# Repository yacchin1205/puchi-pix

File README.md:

# Puchi-Pix (ぷちぴく)

A tiny pixel art display kit powered by STM32G030F6P, with a 96x64 OLED (SSD1331) or TFT display.

## Concept

Puchi-Pix was born from a simple desire: to carry pixel art animations in your pocket.

It pairs an STM32G030F6P with a small OLED, targeting a keychain-sized form factor. Rather than a coin cell with its tedious battery swaps, the board integrates a LiPo charger on-board — unusual for something this small, but essential for a device meant to live in your pocket. Exposed GPIO and an onboard accelerometer also make it a capable dev board.

The STM32G030F6P has just 32KB of flash. Fitting animated pixel art into that space demands inter-frame delta compression, 4-bit palettes, and every byte counted. The kind of constraint that once made a project like this feel out of reach for a weekend hack.

Enter the age of coding agents. What used to take careful hand-optimization now becomes a conversation — iterate on compression schemes, generate frame data, and push against hardware limits at the speed of thought. The constraint doesn't go away, but it stops being a barrier and starts being a craft.

Puchi-Pix is a project built for this era — constrained hardware, creative ambition, and an AI coding agent to bridge the gap.

## STM32G030 BOOT0 pin issue

The factory default option bytes have `nBOOT_SEL=1`, which ignores the physical BOOT0 pin. A fresh (empty flash) chip boots into the bootloader automatically, but once firmware is written, the BOOT button has no effect.

Before the first firmware upload, set `nBOOT_SEL=0` via STM32CubeProgrammer CLI:

```bash
STM32_Programmer_CLI -c port=/dev/cu.usbserial-XXXXX br=115200 -ob nBOOT_SEL=0
```

Verify with:

```bash
STM32_Programmer_CLI -c port=/dev/cu.usbserial-XXXXX br=115200 -ob displ
```

`nBOOT_SEL : 0x0 (BOOT0 signal is defined by BOOT0 pin value (legacy mode))` means BOOT+RST will work.

## ESP32 upload fails despite BOOT+RST

On the ESP32 board, entering the bootloader with BOOT+RST sometimes doesn't take — the upload hangs at `Connecting...` for a while and then errors out with:

```
A fatal error occurred: Failed to connect to ESP32-C3: No serial data received.
```

BOOT (GPIO9) is a strapping pin sampled the moment reset is released, so what matters is the button order, not how long anything is held:

1. Press and **hold** BOOT
2. Press and release RST while still holding BOOT
3. Wait a beat, **then** release BOOT — releasing it before (or together with) RST boots the app normally instead
4. Give the USB port a second or two to re-enumerate, then start the upload

If it still fails, power-cycle the board completely and enter the bootloader
before plugging USB back in (on battery power) — this connects reliably:

1. Unplug USB
2. Slide switch OFF, then back ON
3. BOOT+RST (sequence above)
4. Plug USB back in, wait for the port to appear, then start the upload

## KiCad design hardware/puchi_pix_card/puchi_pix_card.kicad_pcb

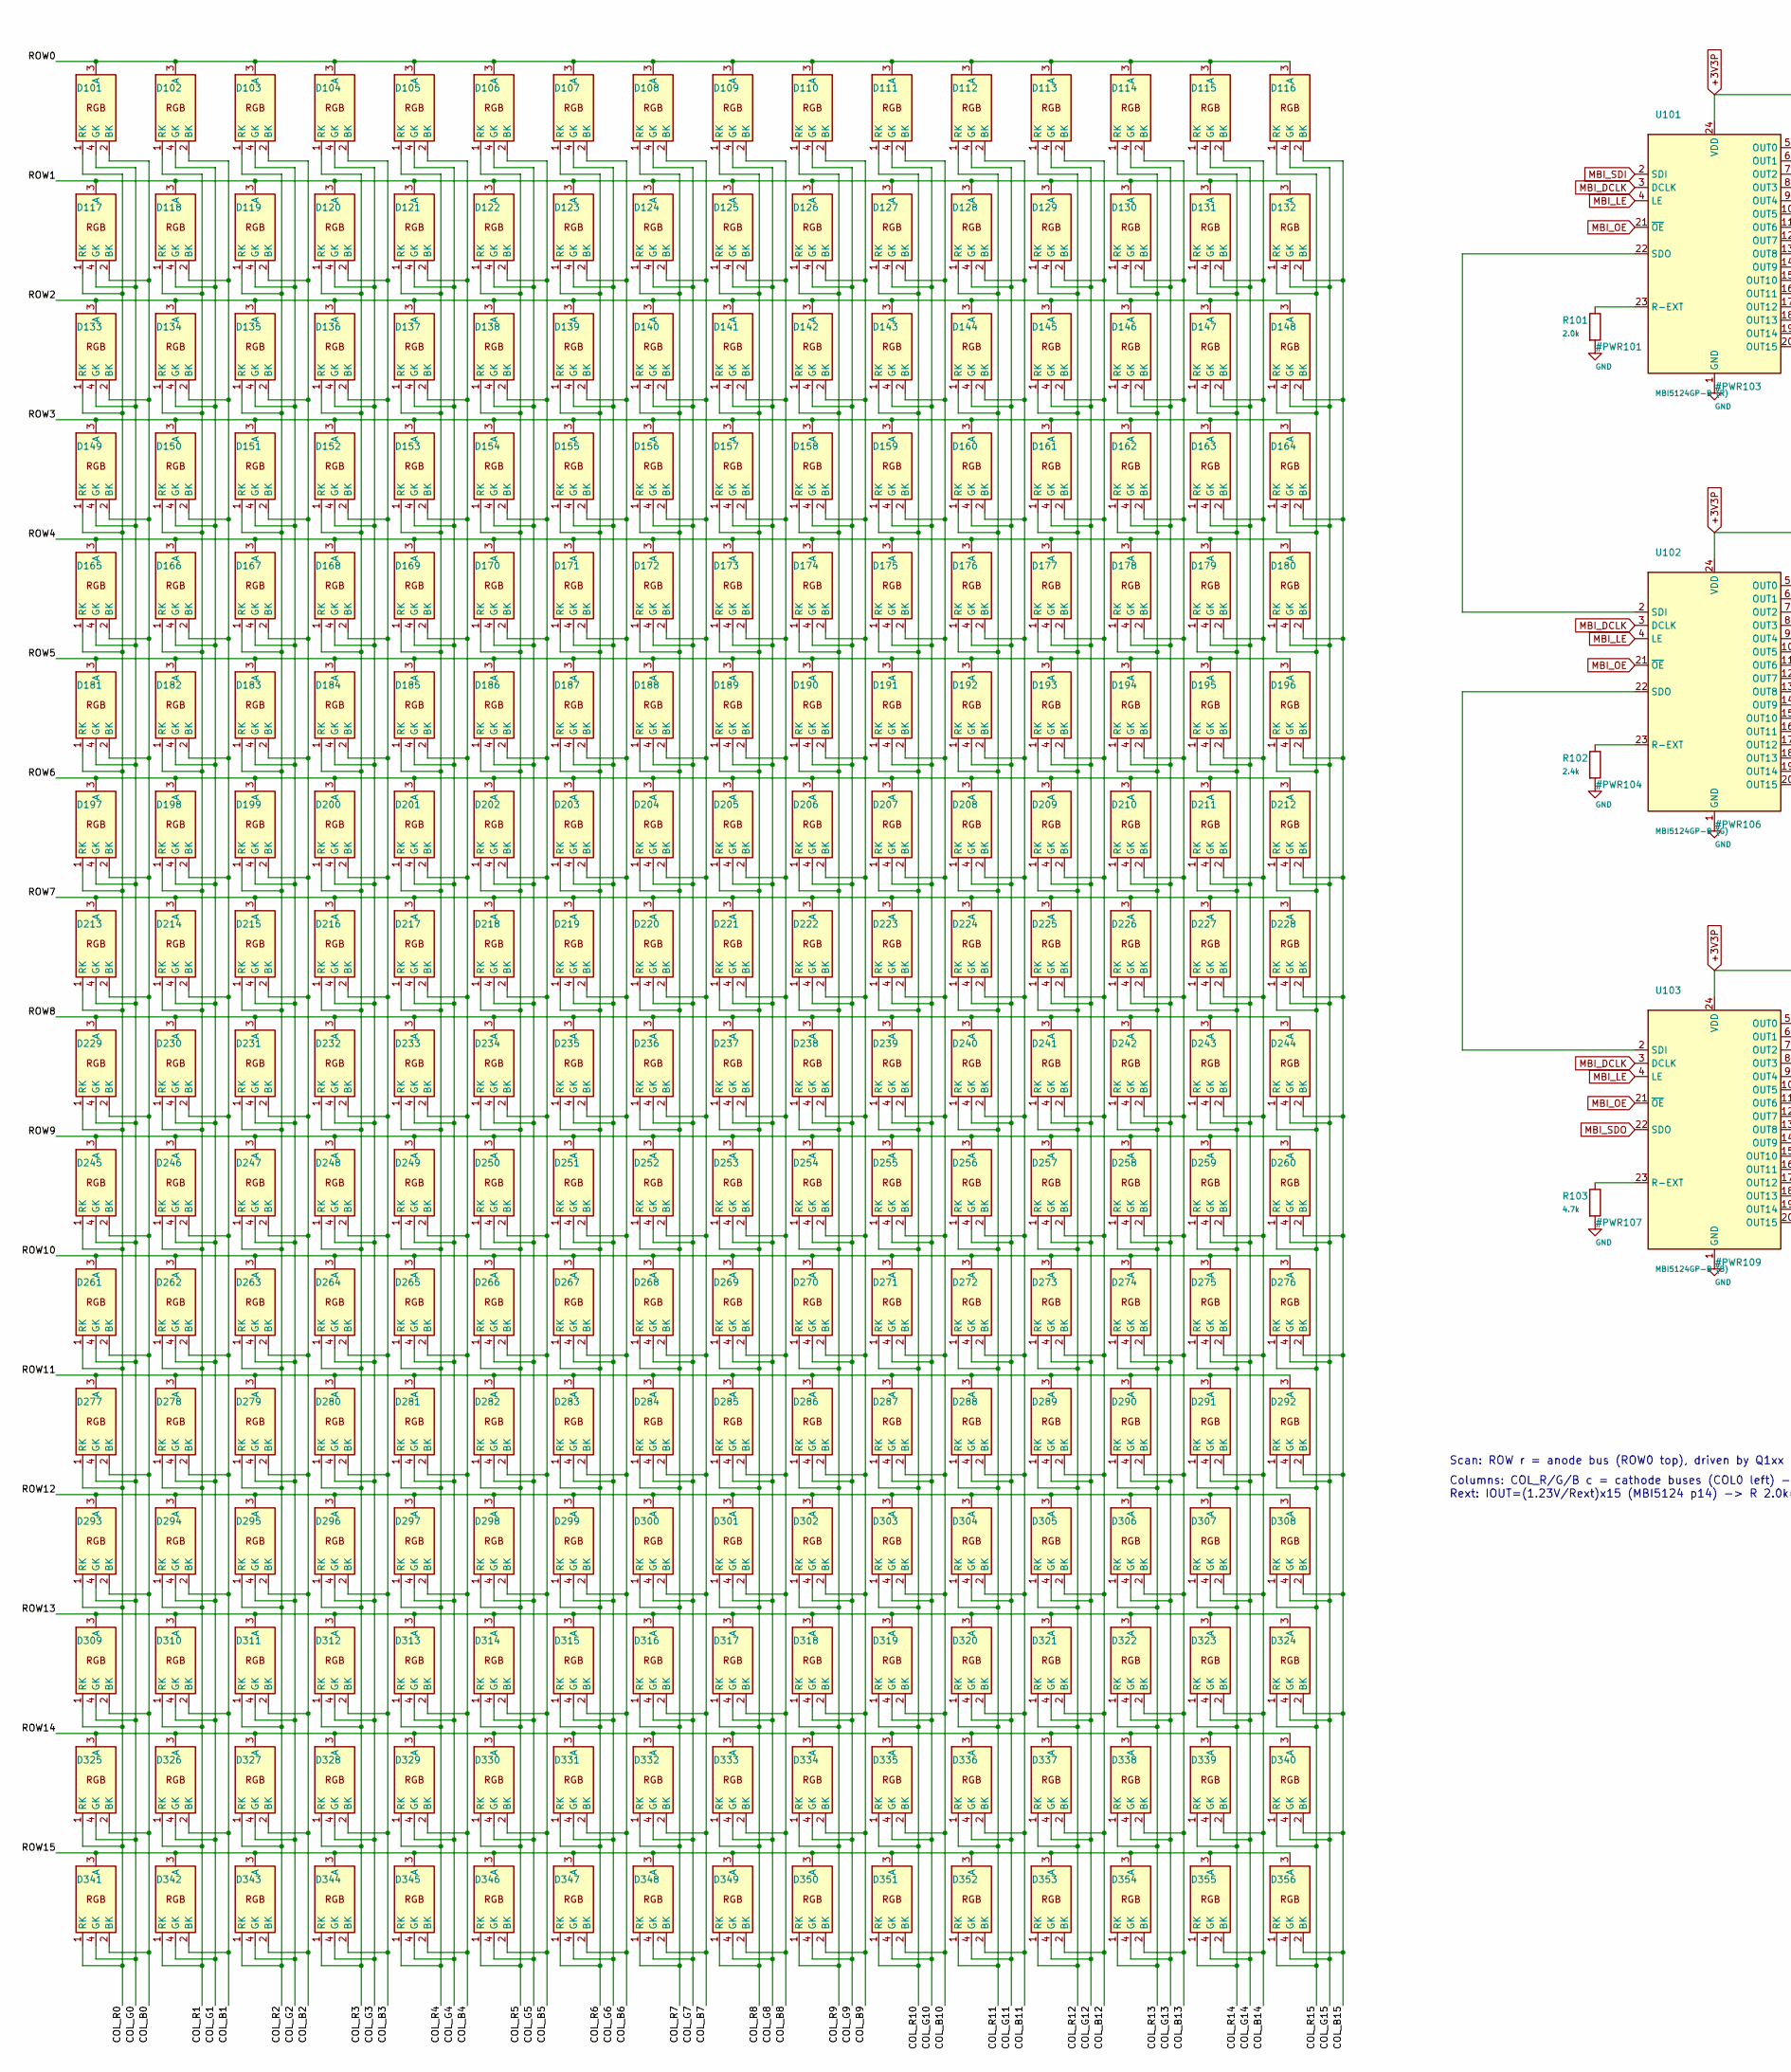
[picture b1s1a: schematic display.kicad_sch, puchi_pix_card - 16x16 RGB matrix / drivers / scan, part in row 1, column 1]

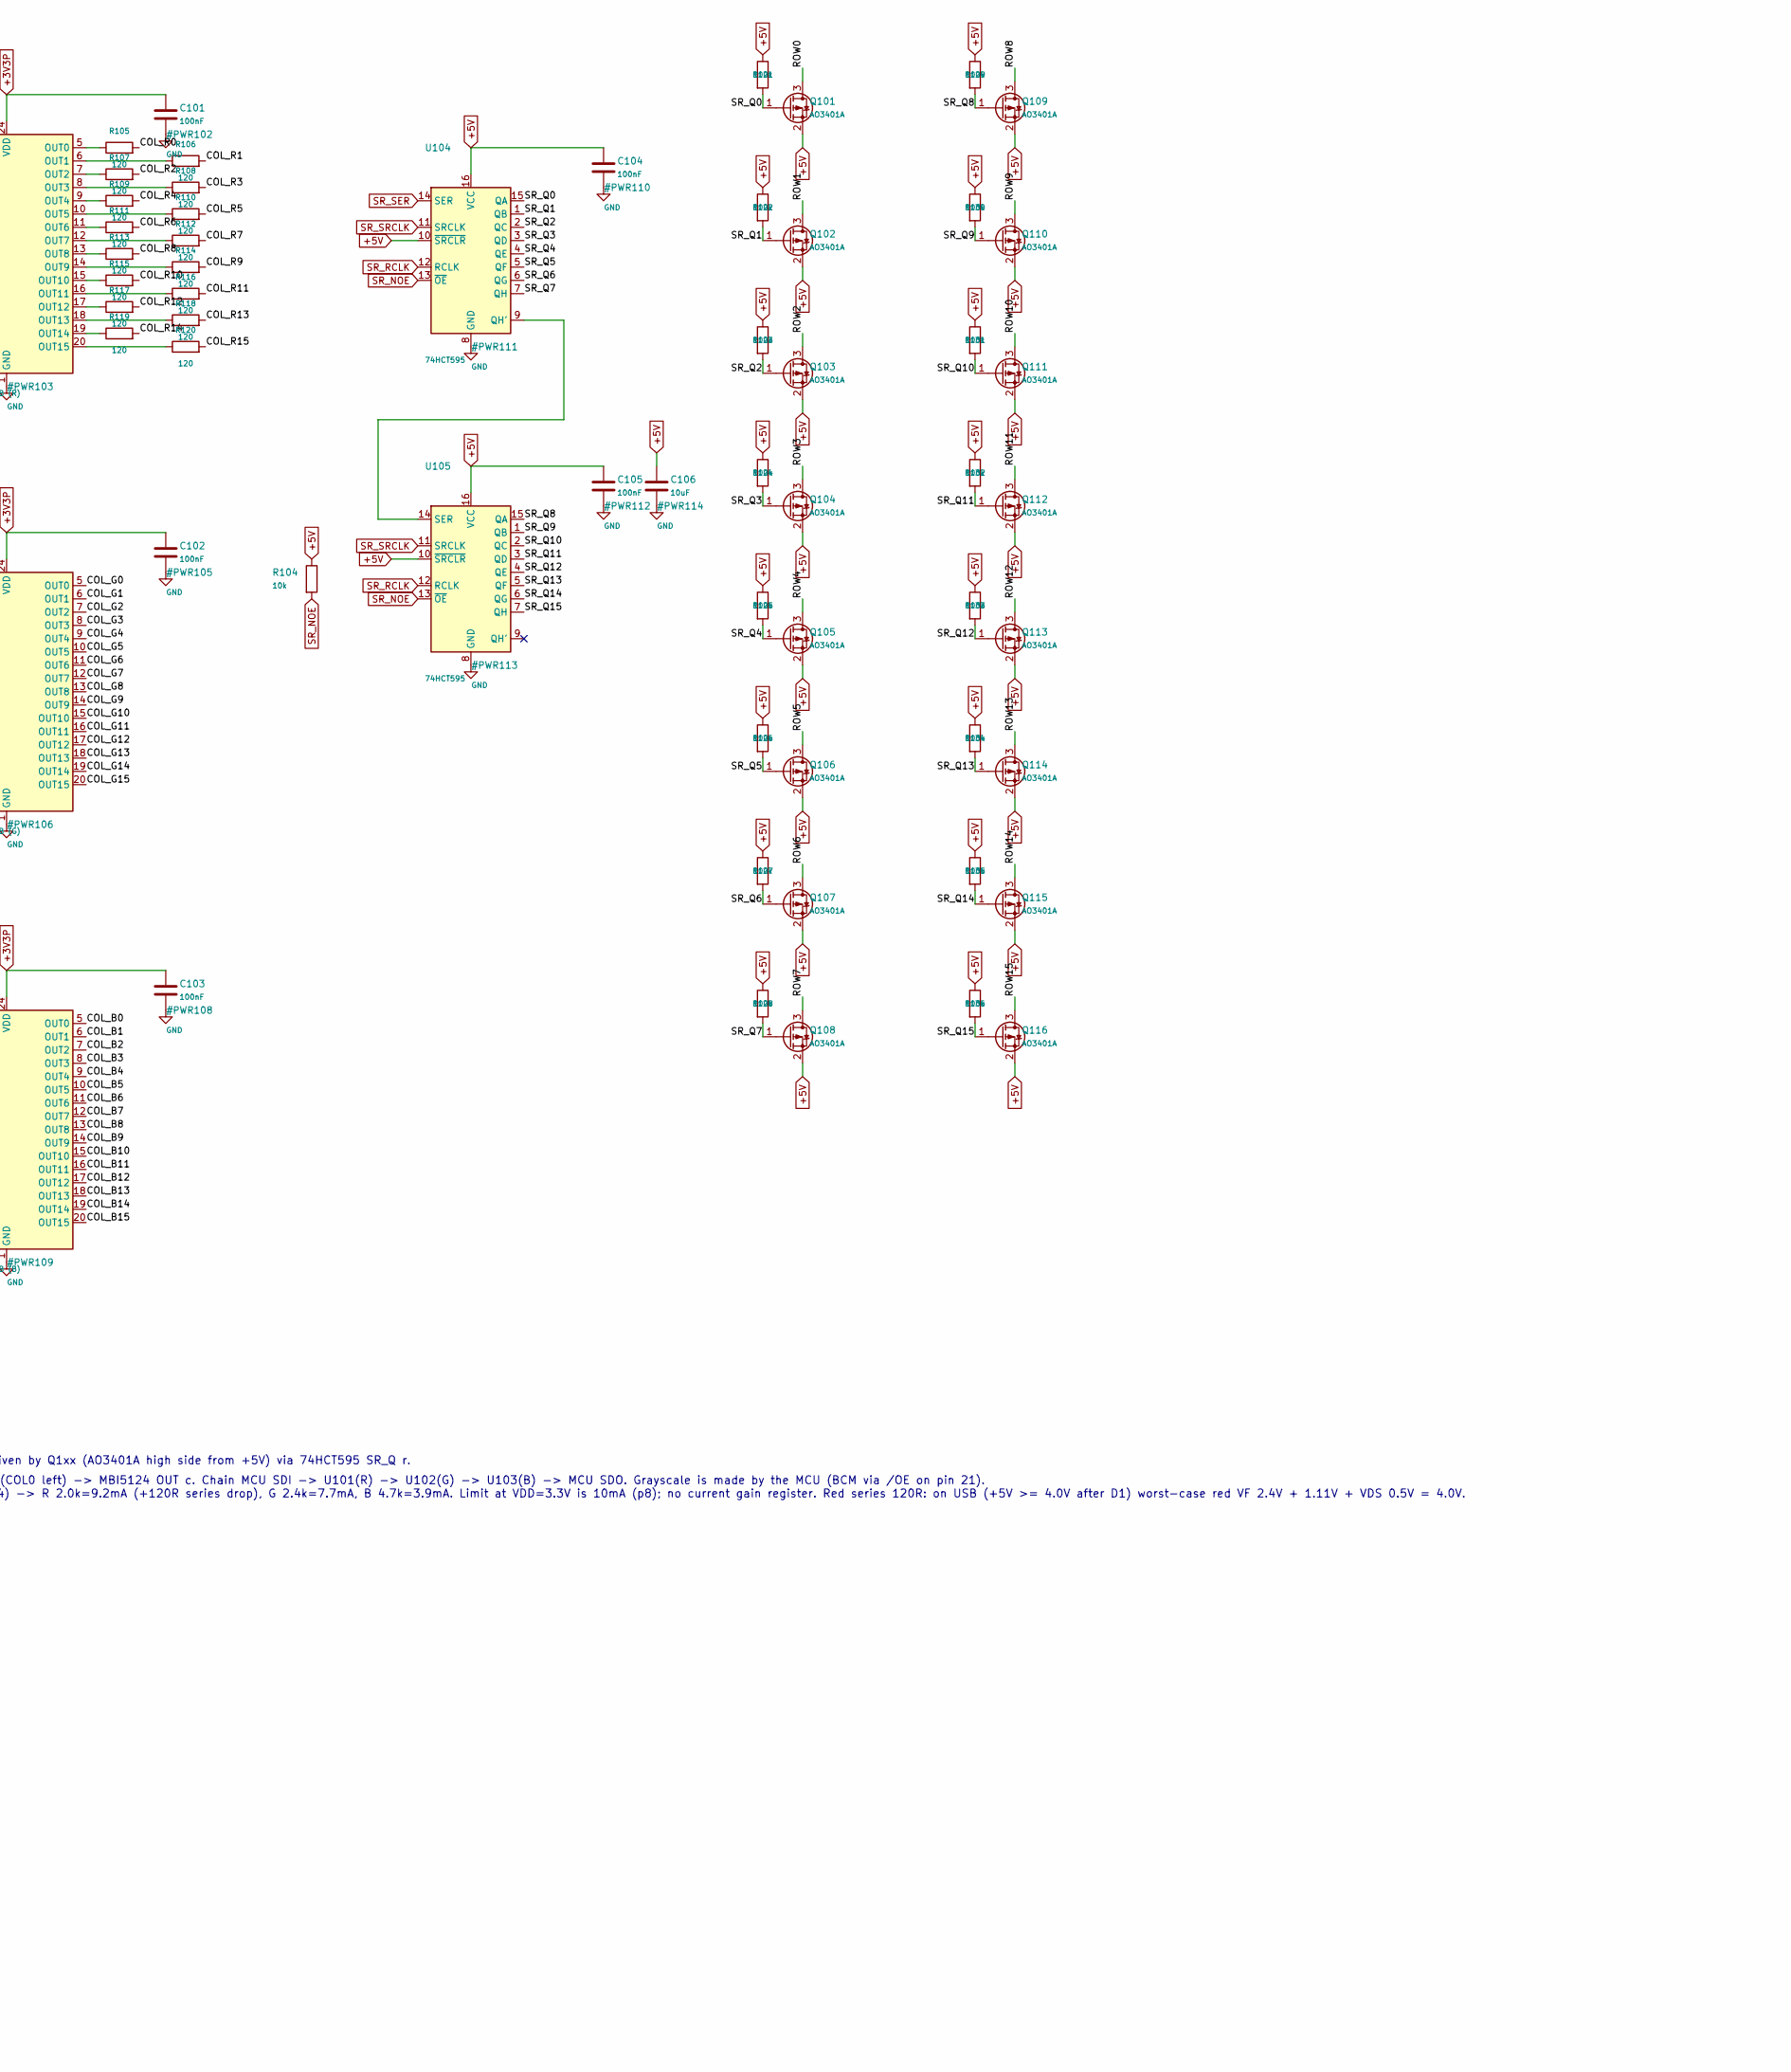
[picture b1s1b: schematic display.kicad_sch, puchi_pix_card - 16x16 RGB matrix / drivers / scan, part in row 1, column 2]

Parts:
C101, C102, C103, C104, C105: 100nF; C_0402_1005Metric; LCSC C309458
C106: 10uF; C_0603_1608Metric; LCSC C96446
D101, D102, D103, D104, D105, D106, D107, D108, D109, D110, D111, D112, D113, D114, D115, D116, D117, D118, D119, D120, D121, D122, D123, D124, D125, D126, D127, D128, D129, D130, D131, D132, D133, D134, D135, D136, D137, D138, D139, D140, D141, D142, D143, D144, D145, D146, D147, D148, D149, D150, D151, D152, D153, D154, D155, D156, D157, D158, D159, D160, D161, D162, D163, D164, D165, D166, D167, D168, D169, D170, D171, D172, D173, D174, D175, D176, D177, D178, D179, D180, D181, D182, D183, D184, D185, D186, D187, D188, D189, D190, D191, D192, D193, D194, D195, D196, D197, D198, D199, D200, D201, D202, D203, D204, D205, D206, D207, D208, D209, D210, D211, D212, D213, D214, D215, D216, D217, D218, D219, D220, D221, D222, D223, D224, D225, D226, D227, D228, D229, D230, D231, D232, D233, D234, D235, D236, D237, D238, D239, D240, D241, D242, D243, D244, D245, D246, D247, D248, D249, D250, D251, D252, D253, D254, D255, D256, D257, D258, D259, D260, D261, D262, D263, D264, D265, D266, D267, D268, D269, D270, D271, D272, D273, D274, D275, D276, D277, D278, D279, D280, D281, D282, D283, D284, D285, D286, D287, D288, D289, D290, D291, D292, D293, D294, D295, D296, D297, D298, D299, D300, D301, D302, D303, D304, D305, D306, D307, D308, D309, D310, D311, D312, D313, D314, D315, D316, D317, D318, D319, D320, D321, D322, D323, D324, D325, D326, D327, D328, D329, D330, D331, D332, D333, D334, D335, D336, D337, D338, D339, D340, D341, D342, D343, D344, D345, D346, D347, D348, D349, D350, D351, D352, D353, D354, D355, D356: FM-B2020RGBA-HG; LED_FM-B2020RGBA; LCSC C42421005
Q101, Q102, Q103, Q104, Q105, Q106, Q107, Q108, Q109, Q110, Q111, Q112, Q113, Q114, Q115, Q116: AO3401A; SOT-23; LCSC C15127
R101: 2.0k; R_0402_1005Metric; LCSC C4109
R102: 2.4k; R_0402_1005Metric; LCSC C25882
R103: 4.7k; R_0402_1005Metric; LCSC C25900
R104: 10k; R_0402_1005Metric; LCSC C25744
R105, R106, R107, R108, R109, R110, R111, R112, R113, R114, R115, R116, R117, R118, R119, R120: 120; R_0402_1005Metric; LCSC C25079
R121, R122, R123, R124, R125, R126, R127, R128, R129, R130, R131, R132, R133, R134, R135, R136: 100k; R_0402_1005Metric; LCSC C25741
U101: MBI5124GP-B (R); SSOP24L-150-0.64; LCSC C256866
U102: MBI5124GP-B (G); SSOP24L-150-0.64; LCSC C256866
U103: MBI5124GP-B (B); SSOP24L-150-0.64; LCSC C256866
U104, U105: 74HCT595; SOIC-16_3.9x9.9mm_P1.27mm; LCSC C282339

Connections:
+3V3P: C101.1, C102.1, C103.1, U101.24 (VDD), U102.24 (VDD), U103.24 (VDD); also elsewhere on the board
+5V: C104.1, C105.1, C106.1, Q101.2 (S), Q102.2 (S), Q103.2 (S), Q104.2 (S), Q105.2 (S), Q106.2 (S), Q107.2 (S), Q108.2 (S), Q109.2 (S), Q110.2 (S), Q111.2 (S), Q112.2 (S), Q113.2 (S), Q114.2 (S), Q115.2 (S), Q116.2 (S), R104.1, R121.1, R122.1, R123.1, R124.1, R125.1, R126.1, R127.1, R128.1, R129.1, R130.1, R131.1, R132.1, R133.1, R134.1, R135.1, R136.1, U104.10 (~SRCLR), U104.16 (VCC), U105.10 (~SRCLR), U105.16 (VCC); also elsewhere on the board
/display/COL_B0: D101.2 (BK), D117.2 (BK), D133.2 (BK), D149.2 (BK), D165.2 (BK), D181.2 (BK), D197.2 (BK), D213.2 (BK), D229.2 (BK), D245.2 (BK), D261.2 (BK), D277.2 (BK), D293.2 (BK), D309.2 (BK), D325.2 (BK), D341.2 (BK), U103.5 (OUT0)
/display/COL_B1: D102.2 (BK), D118.2 (BK), D134.2 (BK), D150.2 (BK), D166.2 (BK), D182.2 (BK), D198.2 (BK), D214.2 (BK), D230.2 (BK), D246.2 (BK), D262.2 (BK), D278.2 (BK), D294.2 (BK), D310.2 (BK), D326.2 (BK), D342.2 (BK), U103.6 (OUT1)
/display/COL_B2: D103.2 (BK), D119.2 (BK), D135.2 (BK), D151.2 (BK), D167.2 (BK), D183.2 (BK), D199.2 (BK), D215.2 (BK), D231.2 (BK), D247.2 (BK), D263.2 (BK), D279.2 (BK), D295.2 (BK), D311.2 (BK), D327.2 (BK), D343.2 (BK), U103.7 (OUT2)
/display/COL_B3: D104.2 (BK), D120.2 (BK), D136.2 (BK), D152.2 (BK), D168.2 (BK), D184.2 (BK), D200.2 (BK), D216.2 (BK), D232.2 (BK), D248.2 (BK), D264.2 (BK), D280.2 (BK), D296.2 (BK), D312.2 (BK), D328.2 (BK), D344.2 (BK), U103.8 (OUT3)
/display/COL_B4: D105.2 (BK), D121.2 (BK), D137.2 (BK), D153.2 (BK), D169.2 (BK), D185.2 (BK), D201.2 (BK), D217.2 (BK), D233.2 (BK), D249.2 (BK), D265.2 (BK), D281.2 (BK), D297.2 (BK), D313.2 (BK), D329.2 (BK), D345.2 (BK), U103.9 (OUT4)
/display/COL_B5: D106.2 (BK), D122.2 (BK), D138.2 (BK), D154.2 (BK), D170.2 (BK), D186.2 (BK), D202.2 (BK), D218.2 (BK), D234.2 (BK), D250.2 (BK), D266.2 (BK), D282.2 (BK), D298.2 (BK), D314.2 (BK), D330.2 (BK), D346.2 (BK), U103.10 (OUT5)
/display/COL_B6: D107.2 (BK), D123.2 (BK), D139.2 (BK), D155.2 (BK), D171.2 (BK), D187.2 (BK), D203.2 (BK), D219.2 (BK), D235.2 (BK), D251.2 (BK), D267.2 (BK), D283.2 (BK), D299.2 (BK), D315.2 (BK), D331.2 (BK), D347.2 (BK), U103.11 (OUT6)
/display/COL_B7: D108.2 (BK), D124.2 (BK), D140.2 (BK), D156.2 (BK), D172.2 (BK), D188.2 (BK), D204.2 (BK), D220.2 (BK), D236.2 (BK), D252.2 (BK), D268.2 (BK), D284.2 (BK), D300.2 (BK), D316.2 (BK), D332.2 (BK), D348.2 (BK), U103.12 (OUT7)
/display/COL_B8: D109.2 (BK), D125.2 (BK), D141.2 (BK), D157.2 (BK), D173.2 (BK), D189.2 (BK), D205.2 (BK), D221.2 (BK), D237.2 (BK), D253.2 (BK), D269.2 (BK), D285.2 (BK), D301.2 (BK), D317.2 (BK), D333.2 (BK), D349.2 (BK), U103.13 (OUT8)
/display/COL_B9: D110.2 (BK), D126.2 (BK), D142.2 (BK), D158.2 (BK), D174.2 (BK), D190.2 (BK), D206.2 (BK), D222.2 (BK), D238.2 (BK), D254.2 (BK), D270.2 (BK), D286.2 (BK), D302.2 (BK), D318.2 (BK), D334.2 (BK), D350.2 (BK), U103.14 (OUT9)
/display/COL_B10: D111.2 (BK), D127.2 (BK), D143.2 (BK), D159.2 (BK), D175.2 (BK), D191.2 (BK), D207.2 (BK), D223.2 (BK), D239.2 (BK), D255.2 (BK), D271.2 (BK), D287.2 (BK), D303.2 (BK), D319.2 (BK), D335.2 (BK), D351.2 (BK), U103.15 (OUT10)
/display/COL_B11: D112.2 (BK), D128.2 (BK), D144.2 (BK), D160.2 (BK), D176.2 (BK), D192.2 (BK), D208.2 (BK), D224.2 (BK), D240.2 (BK), D256.2 (BK), D272.2 (BK), D288.2 (BK), D304.2 (BK), D320.2 (BK), D336.2 (BK), D352.2 (BK), U103.16 (OUT11)
/display/COL_B12: D113.2 (BK), D129.2 (BK), D145.2 (BK), D161.2 (BK), D177.2 (BK), D193.2 (BK), D209.2 (BK), D225.2 (BK), D241.2 (BK), D257.2 (BK), D273.2 (BK), D289.2 (BK), D305.2 (BK), D321.2 (BK), D337.2 (BK), D353.2 (BK), U103.17 (OUT12)
/display/COL_B13: D114.2 (BK), D130.2 (BK), D146.2 (BK), D162.2 (BK), D178.2 (BK), D194.2 (BK), D210.2 (BK), D226.2 (BK), D242.2 (BK), D258.2 (BK), D274.2 (BK), D290.2 (BK), D306.2 (BK), D322.2 (BK), D338.2 (BK), D354.2 (BK), U103.18 (OUT13)
/display/COL_B14: D115.2 (BK), D131.2 (BK), D147.2 (BK), D163.2 (BK), D179.2 (BK), D195.2 (BK), D211.2 (BK), D227.2 (BK), D243.2 (BK), D259.2 (BK), D275.2 (BK), D291.2 (BK), D307.2 (BK), D323.2 (BK), D339.2 (BK), D355.2 (BK), U103.19 (OUT14)
/display/COL_B15: D116.2 (BK), D132.2 (BK), D148.2 (BK), D164.2 (BK), D180.2 (BK), D196.2 (BK), D212.2 (BK), D228.2 (BK), D244.2 (BK), D260.2 (BK), D276.2 (BK), D292.2 (BK), D308.2 (BK), D324.2 (BK), D340.2 (BK), D356.2 (BK), U103.20 (OUT15)
/display/COL_G0: D101.4 (GK), D117.4 (GK), D133.4 (GK), D149.4 (GK), D165.4 (GK), D181.4 (GK), D197.4 (GK), D213.4 (GK), D229.4 (GK), D245.4 (GK), D261.4 (GK), D277.4 (GK), D293.4 (GK), D309.4 (GK), D325.4 (GK), D341.4 (GK), U102.5 (OUT0)
/display/COL_G1: D102.4 (GK), D118.4 (GK), D134.4 (GK), D150.4 (GK), D166.4 (GK), D182.4 (GK), D198.4 (GK), D214.4 (GK), D230.4 (GK), D246.4 (GK), D262.4 (GK), D278.4 (GK), D294.4 (GK), D310.4 (GK), D326.4 (GK), D342.4 (GK), U102.6 (OUT1)
/display/COL_G2: D103.4 (GK), D119.4 (GK), D135.4 (GK), D151.4 (GK), D167.4 (GK), D183.4 (GK), D199.4 (GK), D215.4 (GK), D231.4 (GK), D247.4 (GK), D263.4 (GK), D279.4 (GK), D295.4 (GK), D311.4 (GK), D327.4 (GK), D343.4 (GK), U102.7 (OUT2)
/display/COL_G3: D104.4 (GK), D120.4 (GK), D136.4 (GK), D152.4 (GK), D168.4 (GK), D184.4 (GK), D200.4 (GK), D216.4 (GK), D232.4 (GK), D248.4 (GK), D264.4 (GK), D280.4 (GK), D296.4 (GK), D312.4 (GK), D328.4 (GK), D344.4 (GK), U102.8 (OUT3)
/display/COL_G4: D105.4 (GK), D121.4 (GK), D137.4 (GK), D153.4 (GK), D169.4 (GK), D185.4 (GK), D201.4 (GK), D217.4 (GK), D233.4 (GK), D249.4 (GK), D265.4 (GK), D281.4 (GK), D297.4 (GK), D313.4 (GK), D329.4 (GK), D345.4 (GK), U102.9 (OUT4)
/display/COL_G5: D106.4 (GK), D122.4 (GK), D138.4 (GK), D154.4 (GK), D170.4 (GK), D186.4 (GK), D202.4 (GK), D218.4 (GK), D234.4 (GK), D250.4 (GK), D266.4 (GK), D282.4 (GK), D298.4 (GK), D314.4 (GK), D330.4 (GK), D346.4 (GK), U102.10 (OUT5)
/display/COL_G6: D107.4 (GK), D123.4 (GK), D139.4 (GK), D155.4 (GK), D171.4 (GK), D187.4 (GK), D203.4 (GK), D219.4 (GK), D235.4 (GK), D251.4 (GK), D267.4 (GK), D283.4 (GK), D299.4 (GK), D315.4 (GK), D331.4 (GK), D347.4 (GK), U102.11 (OUT6)
/display/COL_G7: D108.4 (GK), D124.4 (GK), D140.4 (GK), D156.4 (GK), D172.4 (GK), D188.4 (GK), D204.4 (GK), D220.4 (GK), D236.4 (GK), D252.4 (GK), D268.4 (GK), D284.4 (GK), D300.4 (GK), D316.4 (GK), D332.4 (GK), D348.4 (GK), U102.12 (OUT7)
/display/COL_G8: D109.4 (GK), D125.4 (GK), D141.4 (GK), D157.4 (GK), D173.4 (GK), D189.4 (GK), D205.4 (GK), D221.4 (GK), D237.4 (GK), D253.4 (GK), D269.4 (GK), D285.4 (GK), D301.4 (GK), D317.4 (GK), D333.4 (GK), D349.4 (GK), U102.13 (OUT8)
/display/COL_G9: D110.4 (GK), D126.4 (GK), D142.4 (GK), D158.4 (GK), D174.4 (GK), D190.4 (GK), D206.4 (GK), D222.4 (GK), D238.4 (GK), D254.4 (GK), D270.4 (GK), D286.4 (GK), D302.4 (GK), D318.4 (GK), D334.4 (GK), D350.4 (GK), U102.14 (OUT9)
/display/COL_G10: D111.4 (GK), D127.4 (GK), D143.4 (GK), D159.4 (GK), D175.4 (GK), D191.4 (GK), D207.4 (GK), D223.4 (GK), D239.4 (GK), D255.4 (GK), D271.4 (GK), D287.4 (GK), D303.4 (GK), D319.4 (GK), D335.4 (GK), D351.4 (GK), U102.15 (OUT10)
/display/COL_G11: D112.4 (GK), D128.4 (GK), D144.4 (GK), D160.4 (GK), D176.4 (GK), D192.4 (GK), D208.4 (GK), D224.4 (GK), D240.4 (GK), D256.4 (GK), D272.4 (GK), D288.4 (GK), D304.4 (GK), D320.4 (GK), D336.4 (GK), D352.4 (GK), U102.16 (OUT11)
/display/COL_G12: D113.4 (GK), D129.4 (GK), D145.4 (GK), D161.4 (GK), D177.4 (GK), D193.4 (GK), D209.4 (GK), D225.4 (GK), D241.4 (GK), D257.4 (GK), D273.4 (GK), D289.4 (GK), D305.4 (GK), D321.4 (GK), D337.4 (GK), D353.4 (GK), U102.17 (OUT12)
/display/COL_G13: D114.4 (GK), D130.4 (GK), D146.4 (GK), D162.4 (GK), D178.4 (GK), D194.4 (GK), D210.4 (GK), D226.4 (GK), D242.4 (GK), D258.4 (GK), D274.4 (GK), D290.4 (GK), D306.4 (GK), D322.4 (GK), D338.4 (GK), D354.4 (GK), U102.18 (OUT13)
/display/COL_G14: D115.4 (GK), D131.4 (GK), D147.4 (GK), D163.4 (GK), D179.4 (GK), D195.4 (GK), D211.4 (GK), D227.4 (GK), D243.4 (GK), D259.4 (GK), D275.4 (GK), D291.4 (GK), D307.4 (GK), D323.4 (GK), D339.4 (GK), D355.4 (GK), U102.19 (OUT14)
/display/COL_G15: D116.4 (GK), D132.4 (GK), D148.4 (GK), D164.4 (GK), D180.4 (GK), D196.4 (GK), D212.4 (GK), D228.4 (GK), D244.4 (GK), D260.4 (GK), D276.4 (GK), D292.4 (GK), D308.4 (GK), D324.4 (GK), D340.4 (GK), D356.4 (GK), U102.20 (OUT15)
/display/COL_R0: D101.1 (RK), D117.1 (RK), D133.1 (RK), D149.1 (RK), D165.1 (RK), D181.1 (RK), D197.1 (RK), D213.1 (RK), D229.1 (RK), D245.1 (RK), D261.1 (RK), D277.1 (RK), D293.1 (RK), D309.1 (RK), D325.1 (RK), D341.1 (RK), R105.2
/display/COL_R1: D102.1 (RK), D118.1 (RK), D134.1 (RK), D150.1 (RK), D166.1 (RK), D182.1 (RK), D198.1 (RK), D214.1 (RK), D230.1 (RK), D246.1 (RK), D262.1 (RK), D278.1 (RK), D294.1 (RK), D310.1 (RK), D326.1 (RK), D342.1 (RK), R106.2
/display/COL_R2: D103.1 (RK), D119.1 (RK), D135.1 (RK), D151.1 (RK), D167.1 (RK), D183.1 (RK), D199.1 (RK), D215.1 (RK), D231.1 (RK), D247.1 (RK), D263.1 (RK), D279.1 (RK), D295.1 (RK), D311.1 (RK), D327.1 (RK), D343.1 (RK), R107.2
/display/COL_R3: D104.1 (RK), D120.1 (RK), D136.1 (RK), D152.1 (RK), D168.1 (RK), D184.1 (RK), D200.1 (RK), D216.1 (RK), D232.1 (RK), D248.1 (RK), D264.1 (RK), D280.1 (RK), D296.1 (RK), D312.1 (RK), D328.1 (RK), D344.1 (RK), R108.2
/display/COL_R4: D105.1 (RK), D121.1 (RK), D137.1 (RK), D153.1 (RK), D169.1 (RK), D185.1 (RK), D201.1 (RK), D217.1 (RK), D233.1 (RK), D249.1 (RK), D265.1 (RK), D281.1 (RK), D297.1 (RK), D313.1 (RK), D329.1 (RK), D345.1 (RK), R109.2
/display/COL_R5: D106.1 (RK), D122.1 (RK), D138.1 (RK), D154.1 (RK), D170.1 (RK), D186.1 (RK), D202.1 (RK), D218.1 (RK), D234.1 (RK), D250.1 (RK), D266.1 (RK), D282.1 (RK), D298.1 (RK), D314.1 (RK), D330.1 (RK), D346.1 (RK), R110.2
/display/COL_R6: D107.1 (RK), D123.1 (RK), D139.1 (RK), D155.1 (RK), D171.1 (RK), D187.1 (RK), D203.1 (RK), D219.1 (RK), D235.1 (RK), D251.1 (RK), D267.1 (RK), D283.1 (RK), D299.1 (RK), D315.1 (RK), D331.1 (RK), D347.1 (RK), R111.2
/display/COL_R7: D108.1 (RK), D124.1 (RK), D140.1 (RK), D156.1 (RK), D172.1 (RK), D188.1 (RK), D204.1 (RK), D220.1 (RK), D236.1 (RK), D252.1 (RK), D268.1 (RK), D284.1 (RK), D300.1 (RK), D316.1 (RK), D332.1 (RK), D348.1 (RK), R112.2
/display/COL_R8: D109.1 (RK), D125.1 (RK), D141.1 (RK), D157.1 (RK), D173.1 (RK), D189.1 (RK), D205.1 (RK), D221.1 (RK), D237.1 (RK), D253.1 (RK), D269.1 (RK), D285.1 (RK), D301.1 (RK), D317.1 (RK), D333.1 (RK), D349.1 (RK), R113.2
/display/COL_R9: D110.1 (RK), D126.1 (RK), D142.1 (RK), D158.1 (RK), D174.1 (RK), D190.1 (RK), D206.1 (RK), D222.1 (RK), D238.1 (RK), D254.1 (RK), D270.1 (RK), D286.1 (RK), D302.1 (RK), D318.1 (RK), D334.1 (RK), D350.1 (RK), R114.2
/display/COL_R10: D111.1 (RK), D127.1 (RK), D143.1 (RK), D159.1 (RK), D175.1 (RK), D191.1 (RK), D207.1 (RK), D223.1 (RK), D239.1 (RK), D255.1 (RK), D271.1 (RK), D287.1 (RK), D303.1 (RK), D319.1 (RK), D335.1 (RK), D351.1 (RK), R115.2
/display/COL_R11: D112.1 (RK), D128.1 (RK), D144.1 (RK), D160.1 (RK), D176.1 (RK), D192.1 (RK), D208.1 (RK), D224.1 (RK), D240.1 (RK), D256.1 (RK), D272.1 (RK), D288.1 (RK), D304.1 (RK), D320.1 (RK), D336.1 (RK), D352.1 (RK), R116.2
/display/COL_R12: D113.1 (RK), D129.1 (RK), D145.1 (RK), D161.1 (RK), D177.1 (RK), D193.1 (RK), D209.1 (RK), D225.1 (RK), D241.1 (RK), D257.1 (RK), D273.1 (RK), D289.1 (RK), D305.1 (RK), D321.1 (RK), D337.1 (RK), D353.1 (RK), R117.2
/display/COL_R13: D114.1 (RK), D130.1 (RK), D146.1 (RK), D162.1 (RK), D178.1 (RK), D194.1 (RK), D210.1 (RK), D226.1 (RK), D242.1 (RK), D258.1 (RK), D274.1 (RK), D290.1 (RK), D306.1 (RK), D322.1 (RK), D338.1 (RK), D354.1 (RK), R118.2
/display/COL_R14: D115.1 (RK), D131.1 (RK), D147.1 (RK), D163.1 (RK), D179.1 (RK), D195.1 (RK), D211.1 (RK), D227.1 (RK), D243.1 (RK), D259.1 (RK), D275.1 (RK), D291.1 (RK), D307.1 (RK), D323.1 (RK), D339.1 (RK), D355.1 (RK), R119.2
/display/COL_R15: D116.1 (RK), D132.1 (RK), D148.1 (RK), D164.1 (RK), D180.1 (RK), D196.1 (RK), D212.1 (RK), D228.1 (RK), D244.1 (RK), D260.1 (RK), D276.1 (RK), D292.1 (RK), D308.1 (RK), D324.1 (RK), D340.1 (RK), D356.1 (RK), R120.2
/display/ROW0: D101.3 (A), D102.3 (A), D103.3 (A), D104.3 (A), D105.3 (A), D106.3 (A), D107.3 (A), D108.3 (A), D109.3 (A), D110.3 (A), D111.3 (A), D112.3 (A), D113.3 (A), D114.3 (A), D115.3 (A), D116.3 (A), Q101.3 (D)
/display/ROW1: D117.3 (A), D118.3 (A), D119.3 (A), D120.3 (A), D121.3 (A), D122.3 (A), D123.3 (A), D124.3 (A), D125.3 (A), D126.3 (A), D127.3 (A), D128.3 (A), D129.3 (A), D130.3 (A), D131.3 (A), D132.3 (A), Q102.3 (D)
/display/ROW2: D133.3 (A), D134.3 (A), D135.3 (A), D136.3 (A), D137.3 (A), D138.3 (A), D139.3 (A), D140.3 (A), D141.3 (A), D142.3 (A), D143.3 (A), D144.3 (A), D145.3 (A), D146.3 (A), D147.3 (A), D148.3 (A), Q103.3 (D)
/display/ROW3: D149.3 (A), D150.3 (A), D151.3 (A), D152.3 (A), D153.3 (A), D154.3 (A), D155.3 (A), D156.3 (A), D157.3 (A), D158.3 (A), D159.3 (A), D160.3 (A), D161.3 (A), D162.3 (A), D163.3 (A), D164.3 (A), Q104.3 (D)
/display/ROW4: D165.3 (A), D166.3 (A), D167.3 (A), D168.3 (A), D169.3 (A), D170.3 (A), D171.3 (A), D172.3 (A), D173.3 (A), D174.3 (A), D175.3 (A), D176.3 (A), D177.3 (A), D178.3 (A), D179.3 (A), D180.3 (A), Q105.3 (D)
/display/ROW5: D181.3 (A), D182.3 (A), D183.3 (A), D184.3 (A), D185.3 (A), D186.3 (A), D187.3 (A), D188.3 (A), D189.3 (A), D190.3 (A), D191.3 (A), D192.3 (A), D193.3 (A), D194.3 (A), D195.3 (A), D196.3 (A), Q106.3 (D)
/display/ROW6: D197.3 (A), D198.3 (A), D199.3 (A), D200.3 (A), D201.3 (A), D202.3 (A), D203.3 (A), D204.3 (A), D205.3 (A), D206.3 (A), D207.3 (A), D208.3 (A), D209.3 (A), D210.3 (A), D211.3 (A), D212.3 (A), Q107.3 (D)
/display/ROW7: D213.3 (A), D214.3 (A), D215.3 (A), D216.3 (A), D217.3 (A), D218.3 (A), D219.3 (A), D220.3 (A), D221.3 (A), D222.3 (A), D223.3 (A), D224.3 (A), D225.3 (A), D226.3 (A), D227.3 (A), D228.3 (A), Q108.3 (D)
/display/ROW8: D229.3 (A), D230.3 (A), D231.3 (A), D232.3 (A), D233.3 (A), D234.3 (A), D235.3 (A), D236.3 (A), D237.3 (A), D238.3 (A), D239.3 (A), D240.3 (A), D241.3 (A), D242.3 (A), D243.3 (A), D244.3 (A), Q109.3 (D)
/display/ROW9: D245.3 (A), D246.3 (A), D247.3 (A), D248.3 (A), D249.3 (A), D250.3 (A), D251.3 (A), D252.3 (A), D253.3 (A), D254.3 (A), D255.3 (A), D256.3 (A), D257.3 (A), D258.3 (A), D259.3 (A), D260.3 (A), Q110.3 (D)
/display/ROW10: D261.3 (A), D262.3 (A), D263.3 (A), D264.3 (A), D265.3 (A), D266.3 (A), D267.3 (A), D268.3 (A), D269.3 (A), D270.3 (A), D271.3 (A), D272.3 (A), D273.3 (A), D274.3 (A), D275.3 (A), D276.3 (A), Q111.3 (D)
/display/ROW11: D277.3 (A), D278.3 (A), D279.3 (A), D280.3 (A), D281.3 (A), D282.3 (A), D283.3 (A), D284.3 (A), D285.3 (A), D286.3 (A), D287.3 (A), D288.3 (A), D289.3 (A), D290.3 (A), D291.3 (A), D292.3 (A), Q112.3 (D)
/display/ROW12: D293.3 (A), D294.3 (A), D295.3 (A), D296.3 (A), D297.3 (A), D298.3 (A), D299.3 (A), D300.3 (A), D301.3 (A), D302.3 (A), D303.3 (A), D304.3 (A), D305.3 (A), D306.3 (A), D307.3 (A), D308.3 (A), Q113.3 (D)
/display/ROW13: D309.3 (A), D310.3 (A), D311.3 (A), D312.3 (A), D313.3 (A), D314.3 (A), D315.3 (A), D316.3 (A), D317.3 (A), D318.3 (A), D319.3 (A), D320.3 (A), D321.3 (A), D322.3 (A), D323.3 (A), D324.3 (A), Q114.3 (D)
/display/ROW14: D325.3 (A), D326.3 (A), D327.3 (A), D328.3 (A), D329.3 (A), D330.3 (A), D331.3 (A), D332.3 (A), D333.3 (A), D334.3 (A), D335.3 (A), D336.3 (A), D337.3 (A), D338.3 (A), D339.3 (A), D340.3 (A), Q115.3 (D)
/display/ROW15: D341.3 (A), D342.3 (A), D343.3 (A), D344.3 (A), D345.3 (A), D346.3 (A), D347.3 (A), D348.3 (A), D349.3 (A), D350.3 (A), D351.3 (A), D352.3 (A), D353.3 (A), D354.3 (A), D355.3 (A), D356.3 (A), Q116.3 (D)
/display/SR_Q0: Q101.1 (G), R121.2, U104.15 (QA)
/display/SR_Q1: Q102.1 (G), R122.2, U104.1 (QB)
/display/SR_Q2: Q103.1 (G), R123.2, U104.2 (QC)
/display/SR_Q3: Q104.1 (G), R124.2, U104.3 (QD)
/display/SR_Q4: Q105.1 (G), R125.2, U104.4 (QE)
/display/SR_Q5: Q106.1 (G), R126.2, U104.5 (QF)
/display/SR_Q6: Q107.1 (G), R127.2, U104.6 (QG)
/display/SR_Q7: Q108.1 (G), R128.2, U104.7 (QH)
/display/SR_Q8: Q109.1 (G), R129.2, U105.15 (QA)
/display/SR_Q9: Q110.1 (G), R130.2, U105.1 (QB)
/display/SR_Q10: Q111.1 (G), R131.2, U105.2 (QC)
/display/SR_Q11: Q112.1 (G), R132.2, U105.3 (QD)
/display/SR_Q12: Q113.1 (G), R133.2, U105.4 (QE)
/display/SR_Q13: Q114.1 (G), R134.2, U105.5 (QF)
/display/SR_Q14: Q115.1 (G), R135.2, U105.6 (QG)
/display/SR_Q15: Q116.1 (G), R136.2, U105.7 (QH)
GND: C101.2, C102.2, C103.2, C104.2, C105.2, C106.2, R101.2, R102.2, R103.2, U101.1 (GND), U102.1 (GND), U103.1 (GND), U104.8 (GND), U105.8 (GND); also elsewhere on the board
MBI_DCLK: U101.3 (DCLK), U102.3 (DCLK), U103.3 (DCLK); also elsewhere on the board
MBI_LE: U101.4 (LE), U102.4 (LE), U103.4 (LE); also elsewhere on the board
MBI_OE: U101.21 (~OE), U102.21 (~OE), U103.21 (~OE); also elsewhere on the board
MBI_SDI: U101.2 (SDI); also elsewhere on the board
MBI_SDO: U103.22 (SDO); also elsewhere on the board
unnamed: R105.1, U101.5 (OUT0)
unnamed: R106.1, U101.6 (OUT1)
unnamed: R107.1, U101.7 (OUT2)
unnamed: R108.1, U101.8 (OUT3)
unnamed: R109.1, U101.9 (OUT4)
unnamed: R110.1, U101.10 (OUT5)
unnamed: R111.1, U101.11 (OUT6)
unnamed: R112.1, U101.12 (OUT7)
unnamed: R113.1, U101.13 (OUT8)
unnamed: R114.1, U101.14 (OUT9)
unnamed: R115.1, U101.15 (OUT10)
unnamed: R116.1, U101.16 (OUT11)
unnamed: R117.1, U101.17 (OUT12)
unnamed: R118.1, U101.18 (OUT13)
unnamed: R119.1, U101.19 (OUT14)
unnamed: R120.1, U101.20 (OUT15)
unnamed: R101.1, U101.23 (R-EXT)
unnamed: U101.22 (SDO), U102.2 (SDI)
unnamed: R102.1, U102.23 (R-EXT)
unnamed: U102.22 (SDO), U103.2 (SDI)
unnamed: R103.1, U103.23 (R-EXT)
unnamed: U104.9 (QH'), U105.14 (SER)
SR_NOE: R104.2, U104.13 (~OE), U105.13 (~OE); also elsewhere on the board
SR_RCLK: U104.12 (RCLK), U105.12 (RCLK); also elsewhere on the board
SR_SER: U104.14 (SER); also elsewhere on the board
SR_SRCLK: U104.11 (SRCLK), U105.11 (SRCLK); also elsewhere on the board

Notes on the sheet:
Scan: ROW r = anode bus (ROW0 top), driven by Q1xx (AO3401A high side from +5V) via 74HCT595 SR_Q r.
Columns: COL_R/G/B c = cathode buses (COL0 left) -> MBI5124 OUT c. Chain MCU SDI -> U101(R) -> U102(G) -> U103(B) -> MCU SDO. Grayscale is made by the MCU (BCM via /OE on pin 21).
Rext: IOUT=(1.23V/Rext)x15 (MBI5124 p14) -> R 2.0k=9.2mA (+120R series drop), G 2.4k=7.7mA, B 4.7k=3.9mA. Limit at VDD=3.3V is 10mA (p8); no current gain register. Red series 120R: on USB (+5V >= 4.0V after D1) worst-case red VF 2.4V + 1.11V + VDS 0.5V = 4.0V.
